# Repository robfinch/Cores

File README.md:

Cores
=====
RTF's Cores
Use at your own risk.
Welcome to my galaxy of cores.
Contained in the directories are IP cores, source code for digital circuits.
Also included are documentation, test benches, and software samples.

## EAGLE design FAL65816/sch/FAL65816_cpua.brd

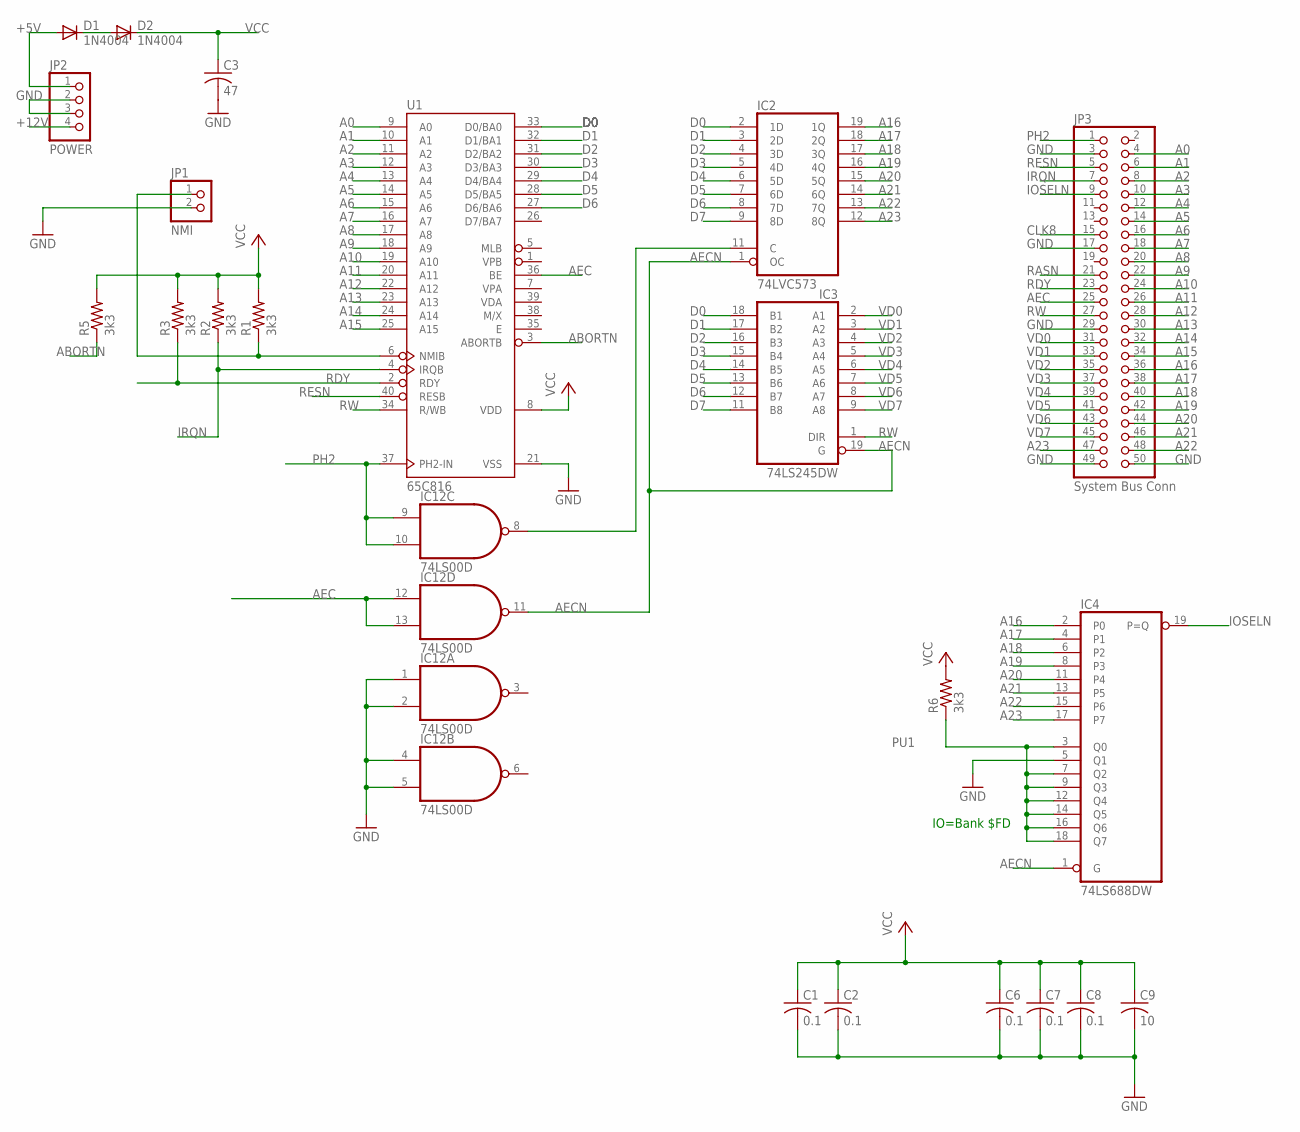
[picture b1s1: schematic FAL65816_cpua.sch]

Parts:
C1, C2, C6, C7, C8: 0.1; C050-024X044
C3: 47; C050-024X044
C9: 10; C050-024X044
D1, D2: 1N4004; DO41-10
IC2: 74LVC573; SO20W
IC3: 74LS245DW; SO20W
IC4: 74LS688DW; SO20W
IC12: 74LS00D; SO14
JP1: NMI; 1X02
JP2: POWER; 1X04/90
JP3: System Bus Conn; 2X25/90
R1, R2, R3, R5: 3k3; 0207/10
R6: 3k3; 0204/7
U1: 65C816; DIP-40

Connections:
+5V: D1.A, JP2.1
+12V: JP2.4
A0: JP3.4, U1.9 (A0)
A1: JP3.6, U1.10 (A1)
A2: JP3.8, U1.11 (A2)
A3: JP3.10, U1.12 (A3)
A4: JP3.12, U1.13 (A4)
A5: JP3.14, U1.14 (A5)
A6: JP3.16, U1.15 (A6)
A7: JP3.18, U1.16 (A7)
A8: JP3.20, U1.17 (A8)
A9: JP3.22, U1.18 (A9)
A10: JP3.24, U1.19 (A10)
A11: JP3.26, U1.20 (A11)
A12: JP3.28, U1.22 (A12)
A13: JP3.30, U1.23 (A13)
A14: JP3.32, U1.24 (A14)
A15: JP3.34, U1.25 (A15)
A16: IC2.19 (1Q), IC4.2 (P0), JP3.36
A17: IC2.18 (2Q), IC4.4 (P1), JP3.38
A18: IC2.17 (3Q), IC4.6 (P2), JP3.40
A19: IC2.16 (4Q), IC4.8 (P3), JP3.42
A20: IC2.15 (5Q), IC4.11 (P4), JP3.44
A21: IC2.14 (6Q), IC4.13 (P5), JP3.46
A22: IC2.13 (7Q), IC4.15 (P6), JP3.48
A23: IC2.12 (8Q), IC4.17 (P7), JP3.47
ABORTN: R5.1, U1.3 (ABORTB)
AEC: IC12.12 (I0), IC12.13 (I1), JP3.25, U1.36 (BE)
AECN: IC2.1 (OC), IC3.19 (G), IC4.1 (G), IC12.11 (O)
CLK8: JP3.15
D0: IC2.2 (1D), IC3.18 (B1), U1.33 (D0/BA0)
D1: IC2.3 (2D), IC3.17 (B2), U1.32 (D1/BA1)
D2: IC2.4 (3D), IC3.16 (B3), U1.31 (D2/BA2)
D3: IC2.5 (4D), IC3.15 (B4), U1.30 (D3/BA3)
D4: IC2.6 (5D), IC3.14 (B5), U1.29 (D4/BA4)
D5: IC2.7 (6D), IC3.13 (B6), U1.28 (D5/BA5)
D6: IC2.8 (7D), IC3.12 (B7), U1.27 (D6/BA6)
D7: IC2.9 (8D), IC3.11 (B8)
GND: C1.2, C2.2, C3.2, C6.2, C7.2, C8.2, C9.2, IC2.10 (GND), IC3.10 (GND), IC4.5 (Q1), IC4.10 (GND), IC12.1 (I0), IC12.2 (I1), IC12.4 (I0), IC12.5 (I1), IC12.7 (GND), JP1.2, JP2.2, JP2.3, JP3.3, JP3.17, JP3.29, JP3.49, JP3.50, U1.21 (VSS)
IOSELN: IC4.19 (P=Q), JP3.9
IRQN: JP3.7, R2.1, U1.4 (IRQB)
unnamed: JP1.1, R1.1, U1.6 (NMIB)
unnamed: IC2.11 (C), IC12.8 (O)
unnamed: D1.C, D2.A
PH2: IC12.9 (I0), IC12.10 (I1), JP3.1, U1.37 (PH2-IN)
PU1: IC4.3 (Q0), IC4.7 (Q2), IC4.9 (Q3), IC4.12 (Q4), IC4.14 (Q5), IC4.16 (Q6), IC4.18 (Q7), R6.1
RASN: JP3.21
RDY: JP3.23, R3.1, U1.2 (RDY)
RESN: JP3.5, U1.40 (RESB)
RW: IC3.1 (DIR), JP3.27, U1.34 (R/WB)
VCC: C1.1, C2.1, C3.1, C6.1, C7.1, C8.1, C9.1, D2.C, IC2.20 (VCC), IC3.20 (VCC), IC4.20 (VCC), IC12.14 (VCC), R1.2, R2.2, R3.2, R5.2, R6.2, U1.8 (VDD)
VD0: IC3.2 (A1), JP3.31
VD1: IC3.3 (A2), JP3.33
VD2: IC3.4 (A3), JP3.35
VD3: IC3.5 (A4), JP3.37
VD4: IC3.6 (A5), JP3.39
VD5: IC3.7 (A6), JP3.41
VD6: IC3.8 (A7), JP3.43
VD7: IC3.9 (A8), JP3.45

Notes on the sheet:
IO=Bank $FD

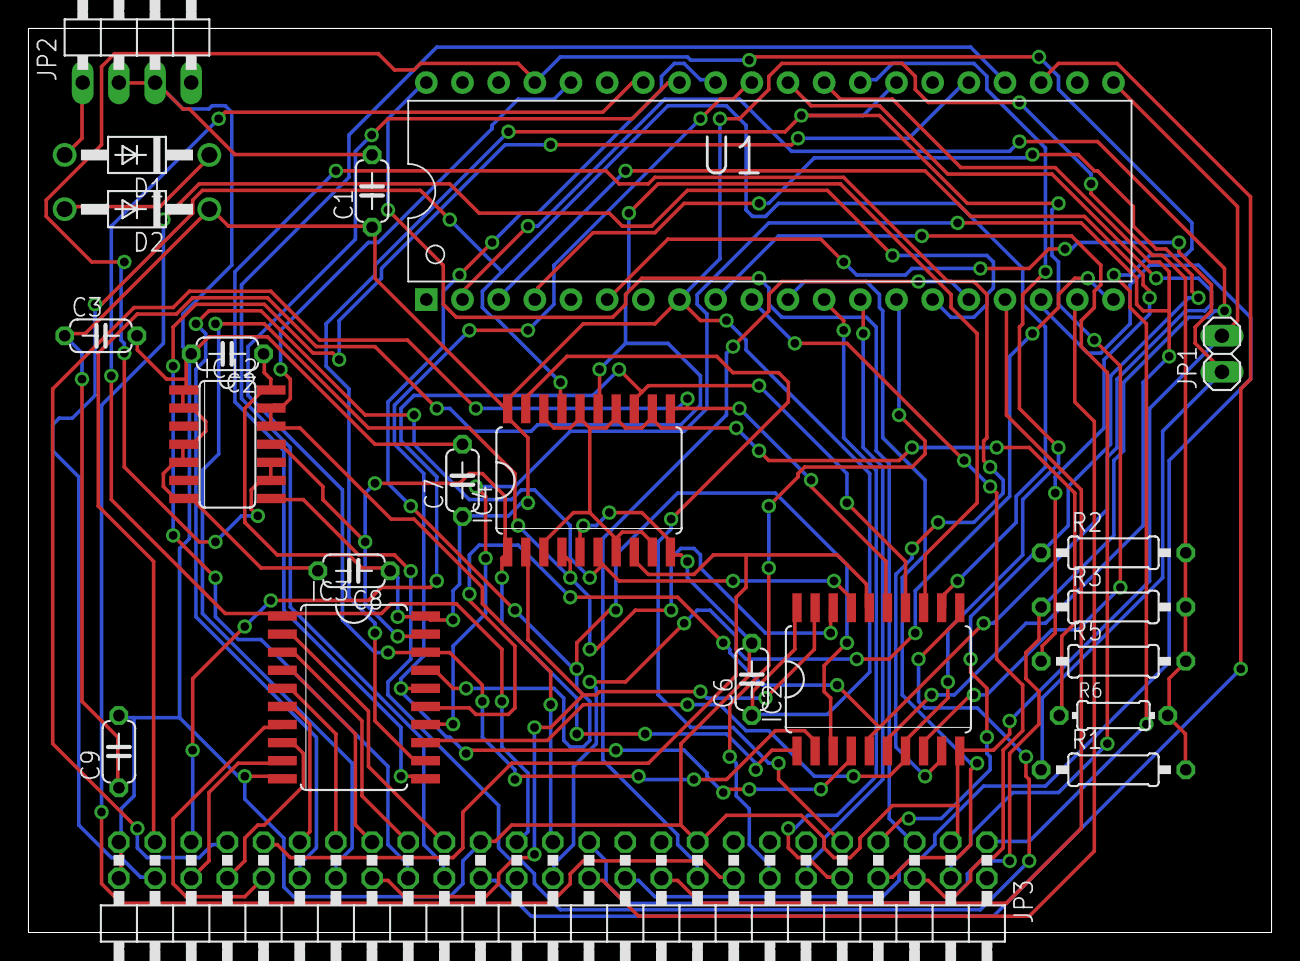
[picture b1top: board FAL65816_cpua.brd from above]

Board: 2 copper layers, 87.3 x 63.5 mm, 22 parts (0 on the bottom side), 56 nets.

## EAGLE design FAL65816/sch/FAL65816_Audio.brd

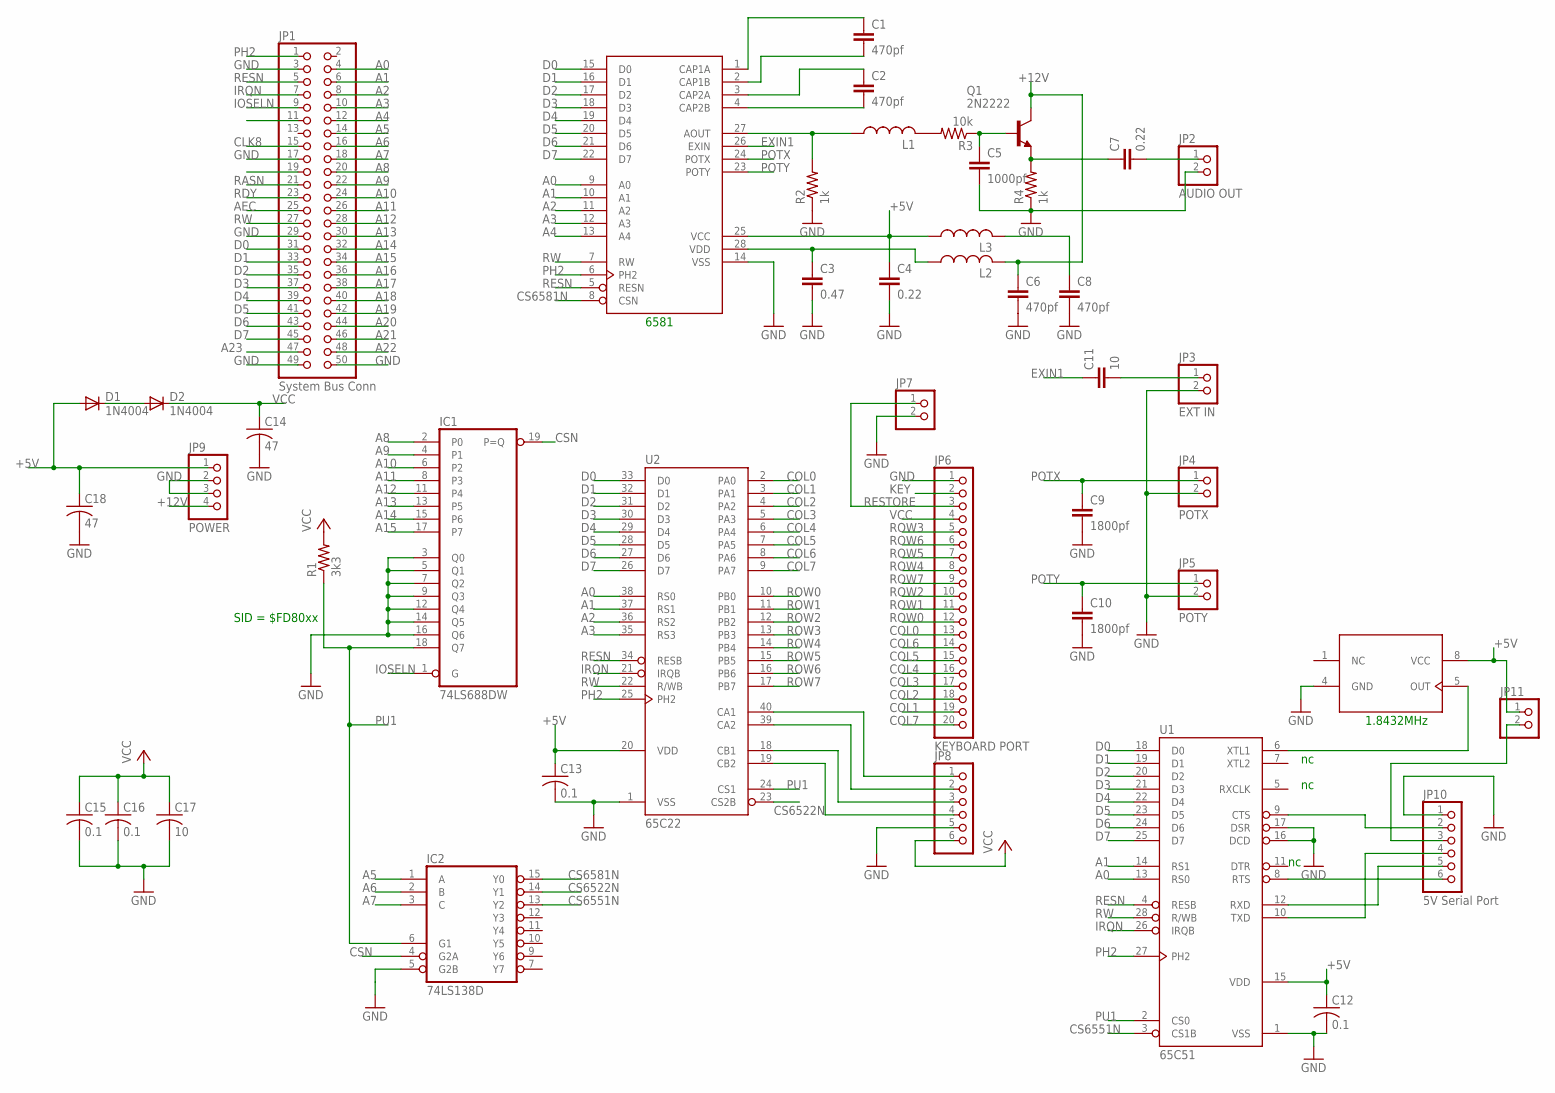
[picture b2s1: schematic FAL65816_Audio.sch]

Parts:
C1, C2, C6, C8: 470pf; C050-024X044
C3: 0.47; C050-024X044
C4, C7: 0.22; C050-024X044
C5: 1000pf; C050-024X044
C9, C10: 1800pf; C050-024X044
C11, C17: 10; C050-024X044
C12, C13, C15, C16: 0.1; C050-024X044
C14, C18: 47; C050-024X044
D1, D2: 1N4004; DO41-10
IC1: 74LS688DW; SO20W
IC2: 74LS138D; SO16
JP1: System Bus Conn; 2X25/90
JP2: AUDIO OUT; 1X02
JP3: EXT IN; 1X02
JP4: POTX; 1X02
JP5: POTY; 1X02
JP6: KEYBOARD PORT; 1X20
JP7, JP11: PINHD-1X2; 1X02
JP8: PINHD-1X6/90; 1X06/90
JP9: POWER; 1X04/90
JP10: 5V Serial Port; 1X06/90
L1, L2, L3: L-US0204/7; 0204/7
Q1: 2N2222; TO18
R1: 3k3; 0204/7
R2, R4: 1k; 0204/7
R3: 10k; 0204/7
U1: 65C51; DIP-28
U2: 65C22; DIP-40
U$1: 6581; DIP-28
U$2: 1.8432MHz; DIL08

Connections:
+5V: C4.1, C12.1, C13.1, C18.1, D1.A, JP9.1, JP11.1, L3.1, U1.15 (VDD), U2.20 (VDD), U$1.25 (VCC), U$2.8 (VCC)
+12V: C6.1, JP9.4, L2.2, Q1.3 (C)
A0: JP1.4, U1.13 (RS0), U2.38 (RS0), U$1.9 (A0)
A1: JP1.6, U1.14 (RS1), U2.37 (RS1), U$1.10 (A1)
A2: JP1.8, U2.36 (RS2), U$1.11 (A2)
A3: JP1.10, U2.35 (RS3), U$1.12 (A3)
A4: JP1.12, U$1.13 (A4)
A5: IC2.1 (A), JP1.14
A6: IC2.2 (B), JP1.16
A7: IC2.3 (C), JP1.18
A8: IC1.2 (P0), JP1.20
A9: IC1.4 (P1), JP1.22
A10: IC1.6 (P2), JP1.24
A11: IC1.8 (P3), JP1.26
A12: IC1.11 (P4), JP1.28
A13: IC1.13 (P5), JP1.30
A14: IC1.15 (P6), JP1.32
A15: IC1.17 (P7), JP1.34
A16: JP1.36
A17: JP1.38
A18: JP1.40
A19: JP1.42
A20: JP1.44
A21: JP1.46
A22: JP1.48
A23: JP1.47
AEC: JP1.25
CLK8: JP1.15
COL0: JP6.13, U2.2 (PA0)
COL1: JP6.19, U2.3 (PA1)
COL2: JP6.18, U2.4 (PA2)
COL3: JP6.17, U2.5 (PA3)
COL4: JP6.16, U2.6 (PA4)
COL5: JP6.15, U2.7 (PA5)
COL6: JP6.14, U2.8 (PA6)
COL7: JP6.20, U2.9 (PA7)
CS6522N: IC2.14 (Y1), U2.23 (CS2B)
CS6551N: IC2.13 (Y2), U1.3 (CS1B)
CS6581N: IC2.15 (Y0), U$1.8 (CSN)
CSN: IC1.19 (P=Q), IC2.4 (G2A)
D0: JP1.31, U1.18 (D0), U2.33 (D0), U$1.15 (D0)
D1: JP1.33, U1.19 (D1), U2.32 (D1), U$1.16 (D1)
D2: JP1.35, U1.20 (D2), U2.31 (D2), U$1.17 (D2)
D3: JP1.37, U1.21 (D3), U2.30 (D3), U$1.18 (D3)
D4: JP1.39, U1.22 (D4), U2.29 (D4), U$1.19 (D4)
D5: JP1.41, U1.23 (D5), U2.28 (D5), U$1.20 (D5)
D6: JP1.43, U1.24 (D6), U2.27 (D6), U$1.21 (D6)
D7: JP1.45, U1.25 (D7), U2.26 (D7), U$1.22 (D7)
EXIN1: C11.1, U$1.26 (EXIN)
GND: C3.2, C4.2, C5.2, C6.2, C8.2, C9.2, C10.2, C12.2, C13.2, C14.2, C15.2, C16.2, C17.2, C18.2, IC1.3 (Q0), IC1.5 (Q1), IC1.7 (Q2), IC1.9 (Q3), IC1.10 (GND), IC1.12 (Q4), IC1.14 (Q5), IC1.16 (Q6), IC2.5 (G2B), IC2.8 (GND), JP1.3, JP1.17, JP1.29, JP1.49, JP1.50, JP2.2, JP3.2, JP4.2, JP5.2, JP6.1, JP7.2, JP8.5, JP9.2, JP9.3, JP10.1, R2.1, R4.1, U1.1 (VSS), U1.16 (DCD), U1.17 (DSR), U2.1 (VSS), U$1.14 (VSS), U$2.4 (GND)
IOSELN: IC1.1 (G), JP1.9
IRQN: JP1.7, U1.26 (IRQB), U2.21 (IRQB)
KEY: JP6.2
unnamed: C1.1, U$1.1 (CAP1A)
unnamed: C1.2, U$1.2 (CAP1B)
unnamed: C2.1, U$1.3 (CAP2A)
unnamed: C2.2, U$1.4 (CAP2B)
unnamed: L1.1, R2.2, U$1.27 (AOUT)
unnamed: C3.1, L2.1, U$1.28 (VDD)
unnamed: L1.2, R3.2
unnamed: C5.1, Q1.2 (B), R3.1
unnamed: C7.1, Q1.1 (E), R4.2
unnamed: D1.C, D2.A
unnamed: C7.2, JP2.1
unnamed: C8.1, L3.2
unnamed: JP10.3, JP11.2
unnamed: C11.2, JP3.1
unnamed: JP10.2, U1.9 (CTS)
unnamed: JP10.4, U1.10 (TXD)
unnamed: JP10.5, U1.12 (RXD)
unnamed: JP10.6, U1.8 (RTS)
unnamed: JP8.1, U2.40 (CA1)
unnamed: JP8.2, U2.39 (CA2)
unnamed: JP8.3, U2.18 (CB1)
unnamed: JP8.4, U2.19 (CB2)
unnamed: U1.6 (XTL1), U$2.5 (OUT)
PH2: JP1.1, U1.27 (PH2), U2.25 (PH2), U$1.6 (PH2)
POTX: C9.1, JP4.1, U$1.24 (POTX)
POTY: C10.1, JP5.1, U$1.23 (POTY)
PU1: IC1.18 (Q7), IC2.6 (G1), R1.1, U1.2 (CS0), U2.24 (CS1)
RASN: JP1.21
RDY: JP1.23
RESN: JP1.5, U1.4 (RESB), U2.34 (RESB), U$1.5 (RESN)
RESTORE: JP6.3, JP7.1
ROW0: JP6.12, U2.10 (PB0)
ROW1: JP6.11, U2.11 (PB1)
ROW2: JP6.10, U2.12 (PB2)
ROW3: JP6.5, U2.13 (PB3)
ROW4: JP6.8, U2.14 (PB4)
ROW5: JP6.7, U2.15 (PB5)
ROW6: JP6.6, U2.16 (PB6)
ROW7: JP6.9, U2.17 (PB7)
RW: JP1.27, U1.28 (R/WB), U2.22 (R/WB), U$1.7 (RW)
VCC: C14.1, C15.1, C16.1, C17.1, D2.C, IC1.20 (VCC), IC2.16 (VCC), JP6.4, JP8.6, R1.2

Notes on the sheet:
SID = $FD80xx
1.8432MHz
6581

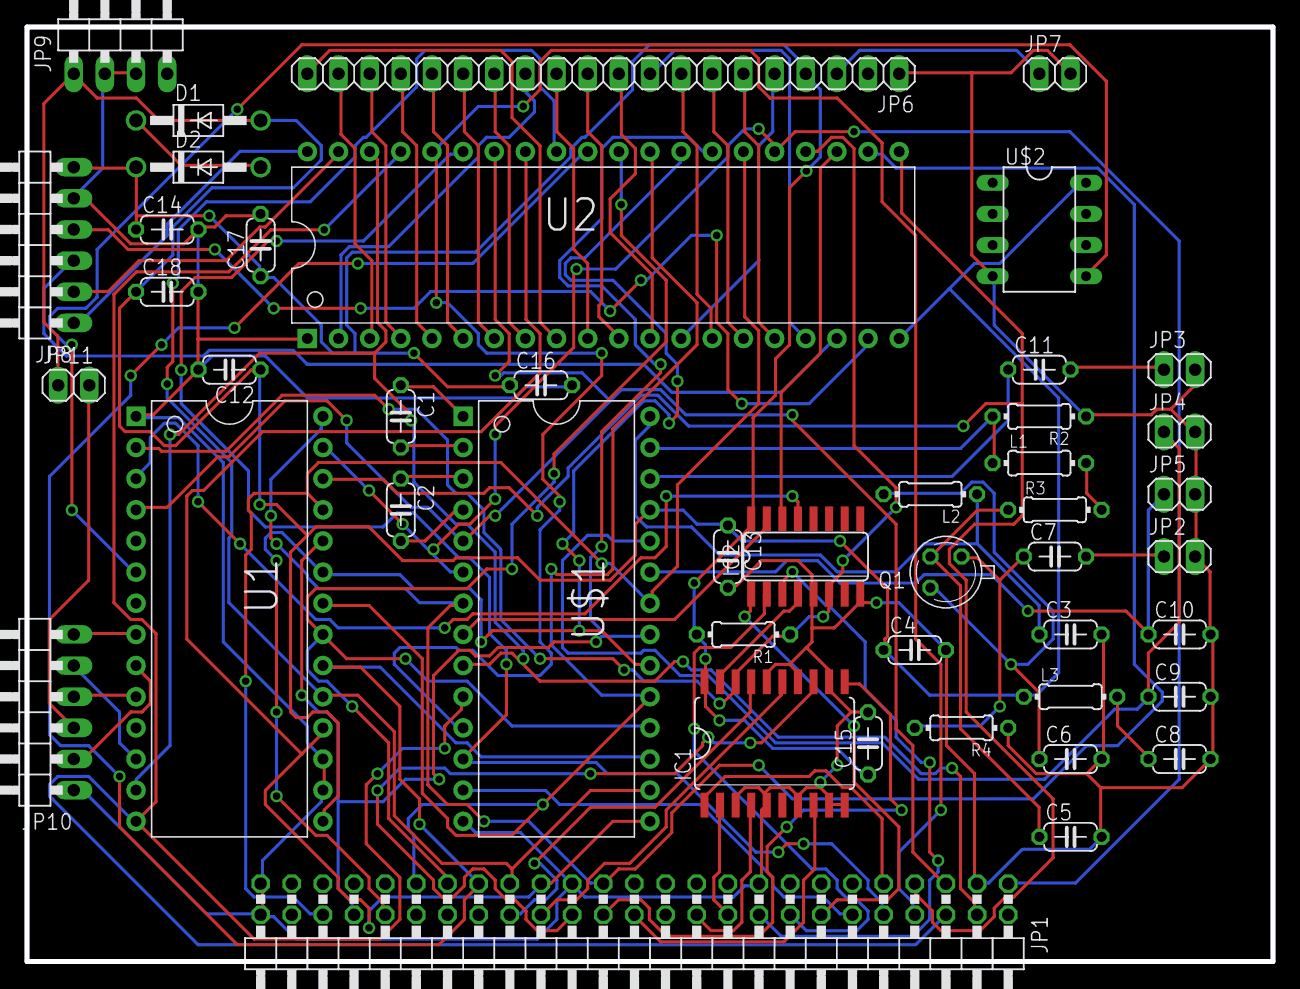
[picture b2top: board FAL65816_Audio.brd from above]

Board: 2 copper layers, 101.6 x 76.2 mm, 45 parts (0 on the bottom side), 81 nets.

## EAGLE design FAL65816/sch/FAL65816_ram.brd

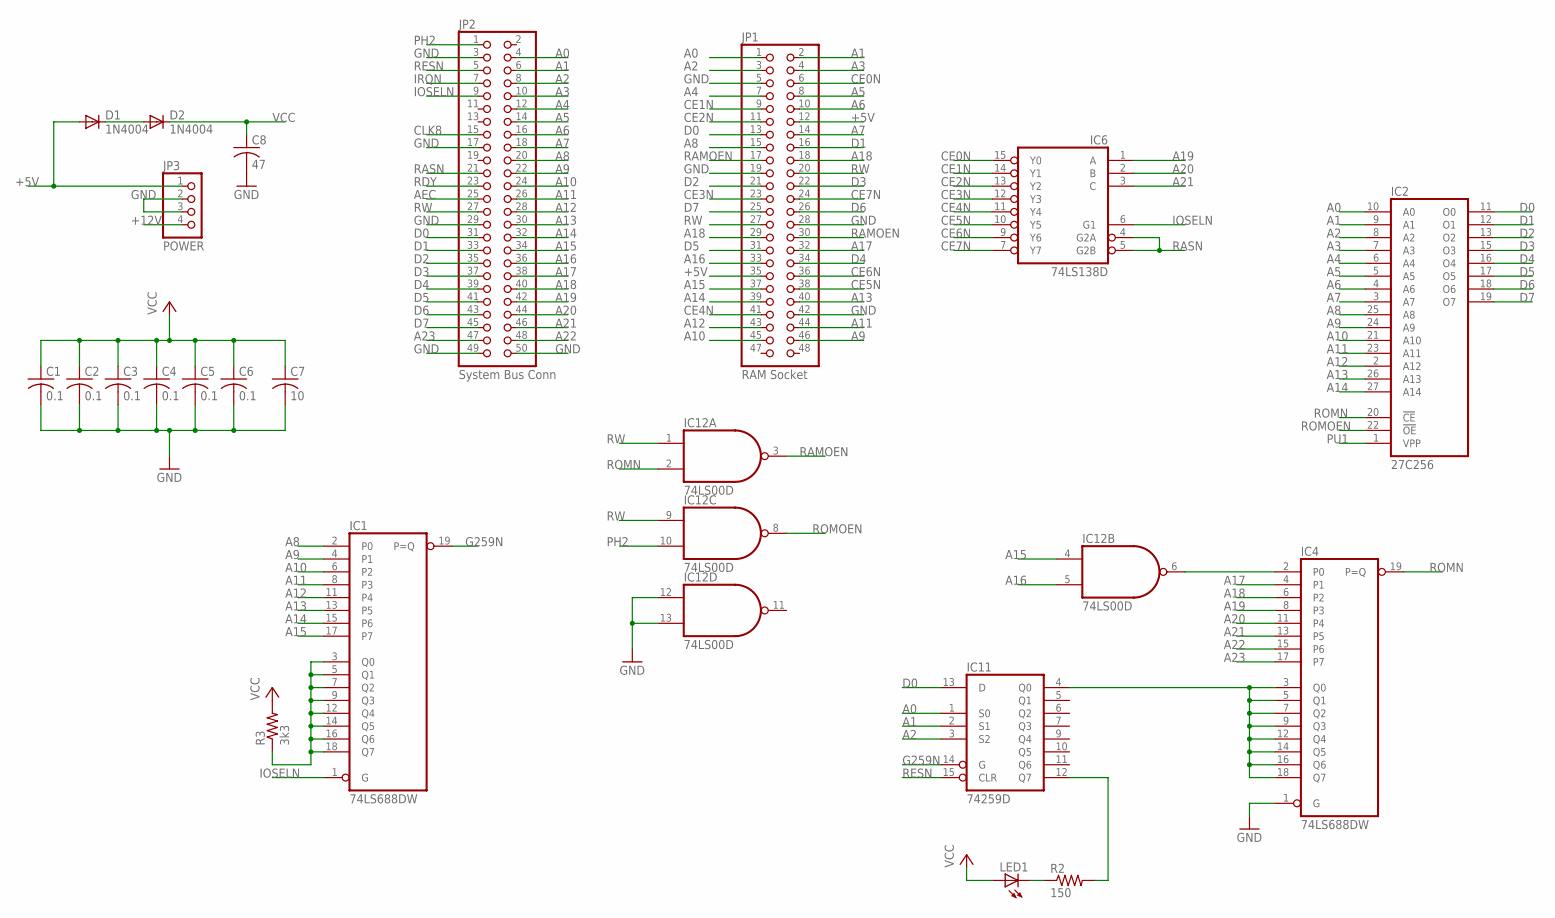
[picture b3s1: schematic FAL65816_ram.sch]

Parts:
C1, C2, C3, C4, C5, C6: 0.1; C050-024X044
C7: 10; C050-024X044
C8: 47; C050-024X044
D1, D2: 1N4004; DO41-10
IC1, IC4: 74LS688DW; SO20W
IC2: 27C256; DIL28
IC6: 74LS138D; SO16
IC11: 74259D; SO16
IC12: 74LS00D; SO14
JP1: RAM Socket; 2X24
JP2: System Bus Conn; 2X25/90
JP3: POWER; 1X04/90
LED1: LED5MM
R2: 150; 0204/7
R3: 3k3; 0204/7

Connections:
+5V: D1.A, JP1.12, JP1.35, JP3.1
+12V: JP3.4
A0: IC2.10 (A0), IC11.1 (S0), JP1.1, JP2.4
A1: IC2.9 (A1), IC11.2 (S1), JP1.2, JP2.6
A2: IC2.8 (A2), IC11.3 (S2), JP1.3, JP2.8
A3: IC2.7 (A3), JP1.4, JP2.10
A4: IC2.6 (A4), JP1.7, JP2.12
A5: IC2.5 (A5), JP1.8, JP2.14
A6: IC2.4 (A6), JP1.10, JP2.16
A7: IC2.3 (A7), JP1.14, JP2.18
A8: IC1.2 (P0), IC2.25 (A8), JP1.15, JP2.20
A9: IC1.4 (P1), IC2.24 (A9), JP1.46, JP2.22
A10: IC1.6 (P2), IC2.21 (A10), JP1.45, JP2.24
A11: IC1.8 (P3), IC2.23 (A11), JP1.44, JP2.26
A12: IC1.11 (P4), IC2.2 (A12), JP1.43, JP2.28
A13: IC1.13 (P5), IC2.26 (A13), JP1.40, JP2.30
A14: IC1.15 (P6), IC2.27 (A14), JP1.39, JP2.32
A15: IC1.17 (P7), IC12.4 (I0), JP1.37, JP2.34
A16: IC12.5 (I1), JP1.33, JP2.36
A17: IC4.4 (P1), JP1.32, JP2.38
A18: IC4.6 (P2), JP1.18, JP1.29, JP2.40
A19: IC4.8 (P3), IC6.1 (A), JP2.42
A20: IC4.11 (P4), IC6.2 (B), JP2.44
A21: IC4.13 (P5), IC6.3 (C), JP2.46
A22: IC4.15 (P6), JP2.48
A23: IC4.17 (P7), JP2.47
AEC: JP2.25
CE0N: IC6.15 (Y0), JP1.6
CE1N: IC6.14 (Y1), JP1.9
CE2N: IC6.13 (Y2), JP1.11
CE3N: IC6.12 (Y3), JP1.23
CE4N: IC6.11 (Y4), JP1.41
CE5N: IC6.10 (Y5), JP1.38
CE6N: IC6.9 (Y6), JP1.36
CE7N: IC6.7 (Y7), JP1.24
CLK8: JP2.15
D0: IC2.11 (O0), IC11.13 (D), JP1.13, JP2.31
D1: IC2.12 (O1), JP1.16, JP2.33
D2: IC2.13 (O2), JP1.21, JP2.35
D3: IC2.15 (O3), JP1.22, JP2.37
D4: IC2.16 (O4), JP1.34, JP2.39
D5: IC2.17 (O5), JP1.31, JP2.41
D6: IC2.18 (O6), JP1.26, JP2.43
D7: IC2.19 (O7), JP1.25, JP2.45
G259N: IC1.19 (P=Q), IC11.14 (G)
GND: C1.2, C2.2, C3.2, C4.2, C5.2, C6.2, C7.2, C8.2, IC1.10 (GND), IC2.14 (GND), IC4.1 (G), IC4.10 (GND), IC6.8 (GND), IC11.8 (GND), IC12.7 (GND), IC12.12 (I0), IC12.13 (I1), JP1.5, JP1.19, JP1.28, JP1.42, JP2.3, JP2.17, JP2.29, JP2.49, JP2.50, JP3.2, JP3.3
IOSELN: IC1.1 (G), IC6.6 (G1), JP2.9
IRQN: JP2.7
unnamed: IC4.3 (Q0), IC4.5 (Q1), IC4.7 (Q2), IC4.9 (Q3), IC4.12 (Q4), IC4.14 (Q5), IC4.16 (Q6), IC4.18 (Q7), IC11.4 (Q0)
unnamed: LED1.K (C), R2.1
unnamed: IC11.12 (Q7), R2.2
unnamed: IC4.2 (P0), IC12.6 (O)
unnamed: D1.C, D2.A
PH2: IC12.10 (I1), JP2.1
PU1: IC1.3 (Q0), IC1.5 (Q1), IC1.7 (Q2), IC1.9 (Q3), IC1.12 (Q4), IC1.14 (Q5), IC1.16 (Q6), IC1.18 (Q7), IC2.1 (VPP), R3.1
RAMOEN: IC12.3 (O), JP1.17, JP1.30
RASN: IC6.4 (G2A), IC6.5 (G2B), JP2.21
RDY: JP2.23
RESN: IC11.15 (CLR), JP2.5
ROMN: IC2.20 (!CE), IC4.19 (P=Q), IC12.2 (I1)
ROMOEN: IC2.22 (!OE), IC12.8 (O)
RW: IC12.1 (I0), IC12.9 (I0), JP1.20, JP1.27, JP2.27
VCC: C1.1, C2.1, C3.1, C4.1, C5.1, C6.1, C7.1, C8.1, D2.C, IC1.20 (VCC), IC2.28 (VCC), IC4.20 (VCC), IC6.16 (VCC), IC11.16 (VCC), IC12.14 (VCC), LED1.A, R3.2

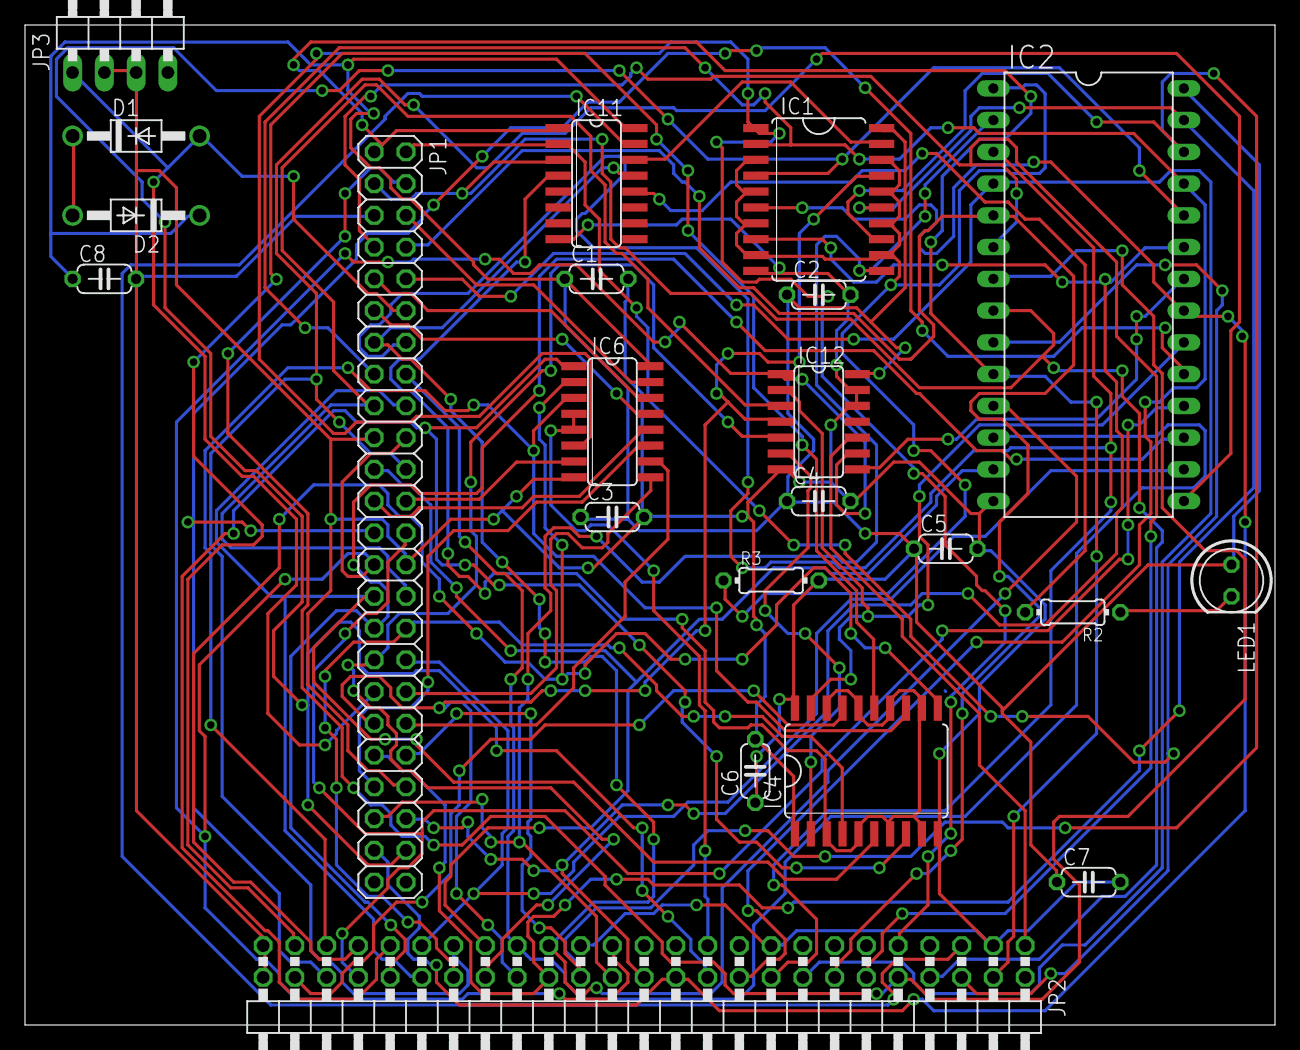
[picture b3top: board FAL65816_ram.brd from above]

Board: 2 copper layers, 100.0 x 80.0 mm, 22 parts (0 on the bottom side), 58 nets.

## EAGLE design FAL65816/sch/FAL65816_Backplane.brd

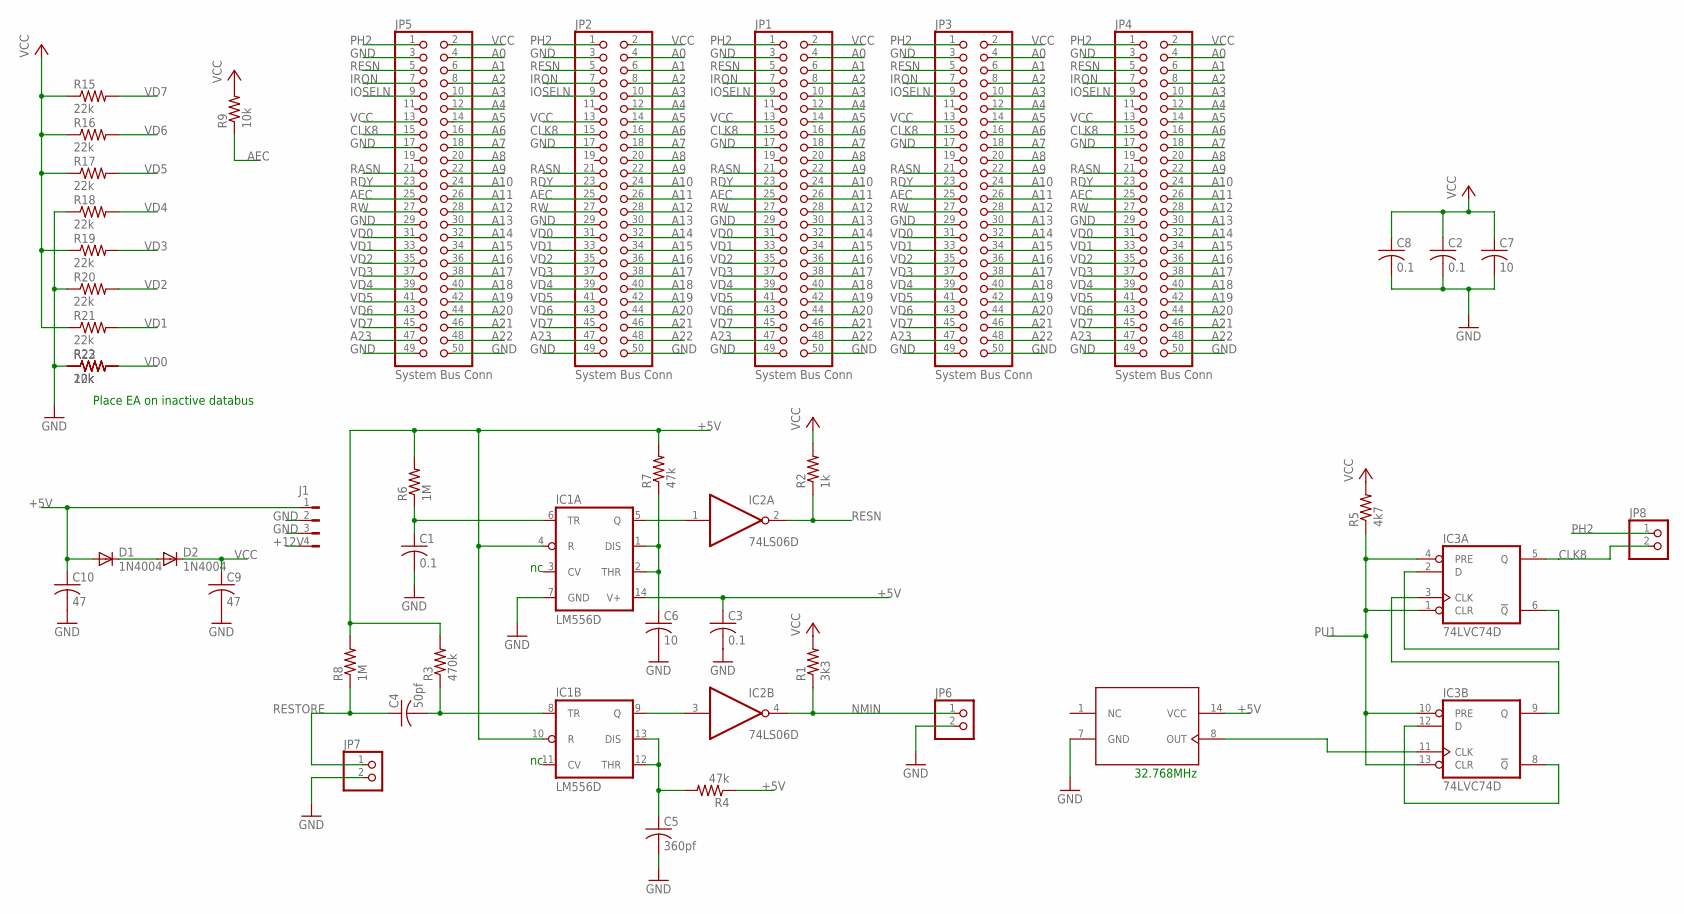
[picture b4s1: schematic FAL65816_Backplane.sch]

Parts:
C1, C2, C3, C8: 0.1; C050-024X044
C4: 50pf; C050-024X044
C5: 360pf; C050-024X044
C6, C7: 10; C050-024X044
C9, C10: 47; C050-024X044
D1, D2: 1N4004; DO41-10
IC1: LM556D; SO14
IC2: 74LS06D; SO14
IC3: 74LVC74D; SO14
J1: FLOPPY-4
JP1, JP2, JP3, JP4, JP5: System Bus Conn; 2X25
JP6, JP7, JP8: PINHD-1X2; 1X02
R1: 3k3; 0204/7
R2: 1k; 0204/7
R3: 470k; 0204/7
R4, R7: 47k; 0204/7
R5: 4k7; 0204/7
R6, R8: 1M; 0204/7
R9: 10k; 0204/7
R15, R16, R17, R18, R19, R20, R21, R23: 22k; 0207/10
R22: 10k; 0207/10
U$1: OSC14; DIL14

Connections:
+5V: C3.1, C10.1, D1.A, IC1.4 (R), IC1.10 (R), IC1.14 (V+), J1.1, R3.2, R4.1, R6.2, R7.2, R8.2, U$1.14 (VCC)
+12V: J1.4
A0: JP1.4, JP2.4, JP3.4, JP4.4, JP5.4
A1: JP1.6, JP2.6, JP3.6, JP4.6, JP5.6
A2: JP1.8, JP2.8, JP3.8, JP4.8, JP5.8
A3: JP1.10, JP2.10, JP3.10, JP4.10, JP5.10
A4: JP1.12, JP2.12, JP3.12, JP4.12, JP5.12
A5: JP1.14, JP2.14, JP3.14, JP4.14, JP5.14
A6: JP1.16, JP2.16, JP3.16, JP4.16, JP5.16
A7: JP1.18, JP2.18, JP3.18, JP4.18, JP5.18
A8: JP1.20, JP2.20, JP3.20, JP4.20, JP5.20
A9: JP1.22, JP2.22, JP3.22, JP4.22, JP5.22
A10: JP1.24, JP2.24, JP3.24, JP4.24, JP5.24
A11: JP1.26, JP2.26, JP3.26, JP4.26, JP5.26
A12: JP1.28, JP2.28, JP3.28, JP4.28, JP5.28
A13: JP1.30, JP2.30, JP3.30, JP4.30, JP5.30
A14: JP1.32, JP2.32, JP3.32, JP4.32, JP5.32
A15: JP1.34, JP2.34, JP3.34, JP4.34, JP5.34
A16: JP1.36, JP2.36, JP3.36, JP4.36, JP5.36
A17: JP1.38, JP2.38, JP3.38, JP4.38, JP5.38
A18: JP1.40, JP2.40, JP3.40, JP4.40, JP5.40
A19: JP1.42, JP2.42, JP3.42, JP4.42, JP5.42
A20: JP1.44, JP2.44, JP3.44, JP4.44, JP5.44
A21: JP1.46, JP2.46, JP3.46, JP4.46, JP5.46
A22: JP1.48, JP2.48, JP3.48, JP4.48, JP5.48
A23: JP1.47, JP2.47, JP3.47, JP4.47, JP5.47
AEC: JP1.25, JP2.25, JP3.25, JP4.25, JP5.25, R9.1
CLK8: IC3.5 (Q), JP1.15, JP2.15, JP3.15, JP4.15, JP5.15, JP8.2
GND: C1.2, C2.2, C3.2, C5.2, C6.2, C7.2, C8.2, C9.2, C10.2, IC1.7 (GND), IC2.7 (GND), IC3.7 (GND), J1.2, J1.3, JP1.3, JP1.17, JP1.29, JP1.49, JP1.50, JP2.3, JP2.17, JP2.29, JP2.49, JP2.50, JP3.3, JP3.17, JP3.29, JP3.49, JP3.50, JP4.3, JP4.17, JP4.29, JP4.49, JP4.50, JP5.3, JP5.17, JP5.29, JP5.49, JP5.50, JP6.2, JP7.2, R18.1, R20.1, R22.1, R23.1, U$1.7 (GND)
IOSELN: JP1.9, JP2.9, JP3.9, JP4.9, JP5.9
IRQN: JP1.7, JP2.7, JP3.7, JP4.7, JP5.7
unnamed: IC3.3 (CLK), IC3.9 (Q)
unnamed: IC1.5 (Q), IC2.1 (I)
unnamed: IC3.8 (!Q), IC3.12 (D)
unnamed: IC1.9 (Q), IC2.3 (I)
unnamed: C1.1, IC1.6 (TR), R6.1
unnamed: IC3.11 (CLK), U$1.8 (OUT)
unnamed: IC3.2 (D), IC3.6 (!Q)
unnamed: R22.2, R23.2
unnamed: C6.1, IC1.1 (DIS), IC1.2 (THR), R7.1
unnamed: C4.2, IC1.8 (TR), R3.1
unnamed: D1.C, D2.A
unnamed: C5.1, IC1.12 (THR), IC1.13 (DIS), R4.2
NMIN: IC2.4 (O), JP6.1, R1.1
PH2: JP1.1, JP2.1, JP3.1, JP4.1, JP5.1, JP8.1
PU1: IC3.1 (CLR), IC3.4 (PRE), IC3.10 (PRE), IC3.13 (CLR), R5.1
RASN: JP1.21, JP2.21, JP3.21, JP4.21, JP5.21
RDY: JP1.23, JP2.23, JP3.23, JP4.23, JP5.23
RESN: IC2.2 (O), JP1.5, JP2.5, JP3.5, JP4.5, JP5.5, R2.1
RESTORE: C4.1, JP7.1, R8.1
RW: JP1.27, JP2.27, JP3.27, JP4.27, JP5.27
VCC: C2.1, C7.1, C8.1, C9.1, D2.C, IC2.14 (VCC), IC3.14 (VCC), JP1.2, JP1.13, JP2.2, JP2.13, JP3.2, JP3.13, JP4.2, JP4.13, JP5.2, JP5.13, R1.2, R2.2, R5.2, R9.2, R15.1, R16.1, R17.1, R19.1, R21.1
VD0: JP1.31, JP2.31, JP3.31, JP4.31, JP5.31
VD1: JP1.33, JP2.33, JP3.33, JP4.33, JP5.33, R21.2
VD2: JP1.35, JP2.35, JP3.35, JP4.35, JP5.35, R20.2
VD3: JP1.37, JP2.37, JP3.37, JP4.37, JP5.37, R19.2
VD4: JP1.39, JP2.39, JP3.39, JP4.39, JP5.39, R18.2
VD5: JP1.41, JP2.41, JP3.41, JP4.41, JP5.41, R17.2
VD6: JP1.43, JP2.43, JP3.43, JP4.43, JP5.43, R16.2
VD7: JP1.45, JP2.45, JP3.45, JP4.45, JP5.45, R15.2

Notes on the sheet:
32.768MHz
Place EA on inactive databus

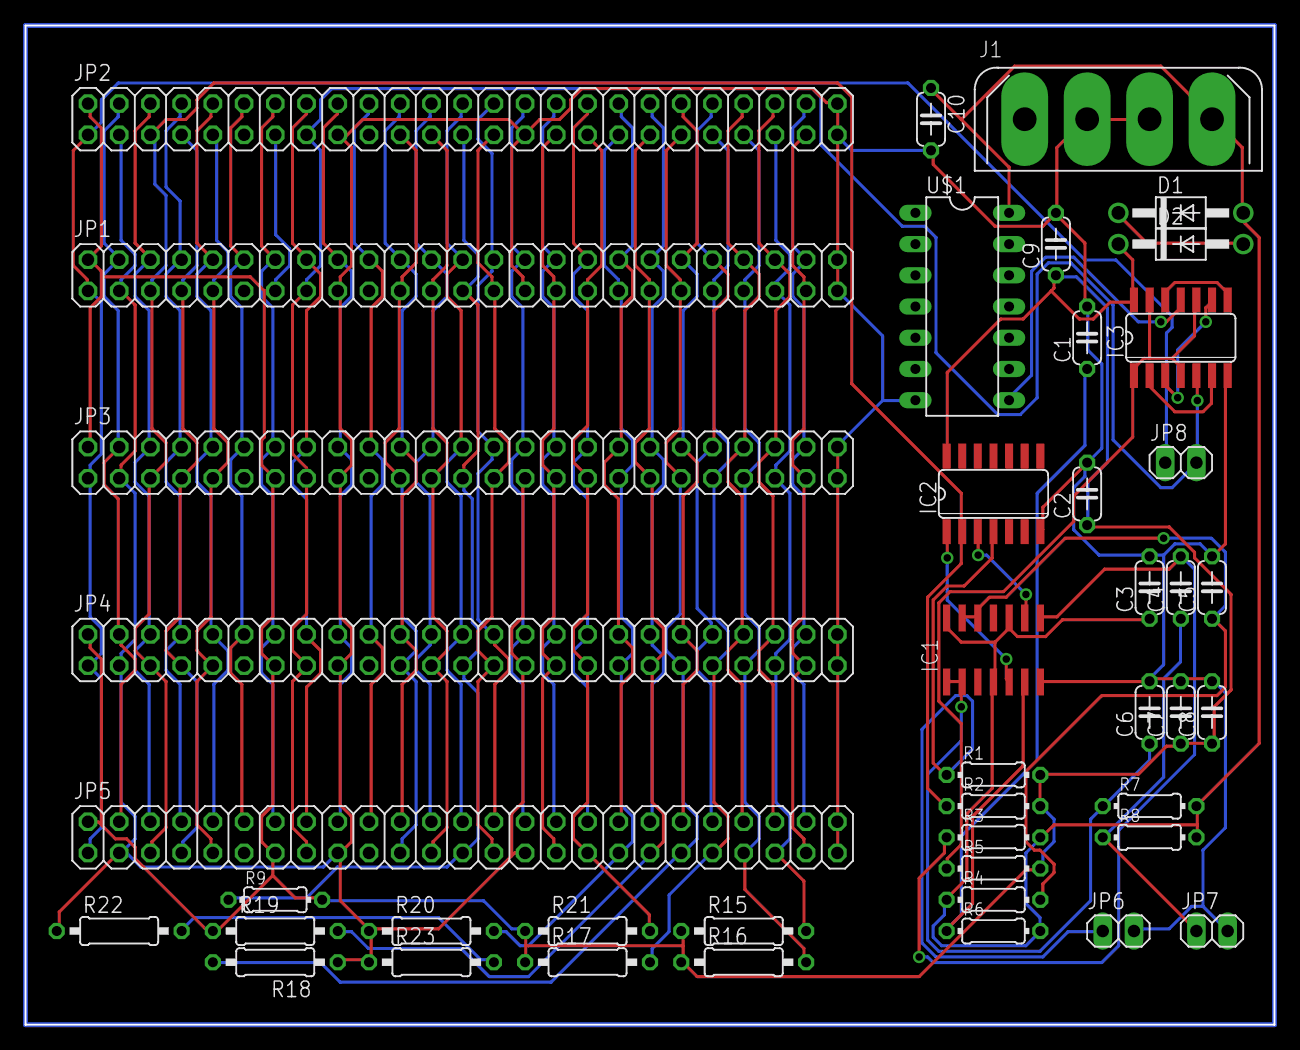
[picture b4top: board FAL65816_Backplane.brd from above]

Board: 2 copper layers, 101.6 x 81.3 mm, 43 parts (0 on the bottom side), 59 nets.
